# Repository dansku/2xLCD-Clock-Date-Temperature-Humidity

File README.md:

2xLCD Clock-Date-Temperature-Humidity

Under dev...

More at: danielandrade.net

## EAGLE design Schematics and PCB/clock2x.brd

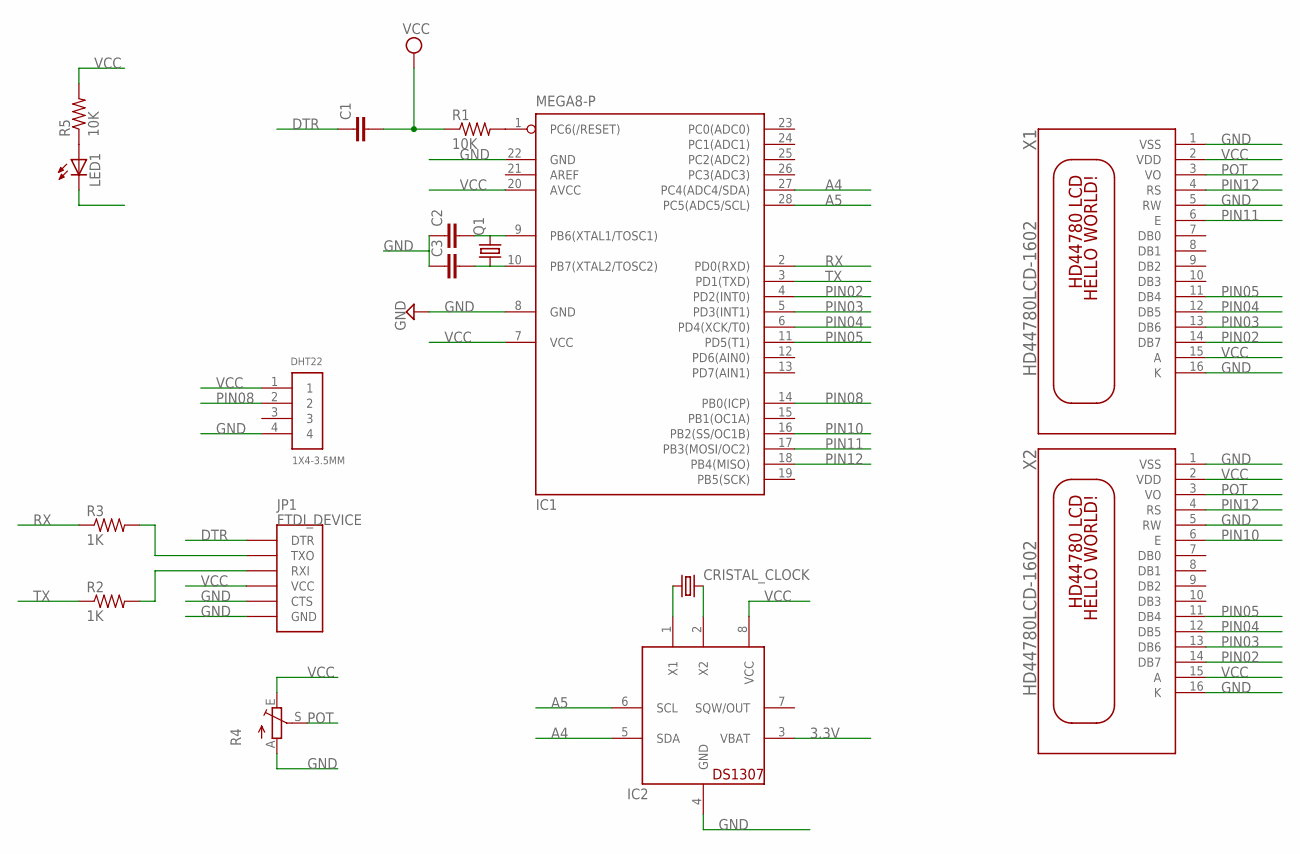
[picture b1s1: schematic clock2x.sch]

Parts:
C1, C2, C3: C5/2.5; C5B2.5
CRISTAL_CLOCK: CRYSTALTC26V; TC26V
DHT22: 1X4-3.5MM; 1X04-3.5MM
IC1: MEGA8-P; DIL28-3
IC2: DS1307; DIL08
JP1: FTDI_DEVICE; FTDI_DEVICE_SIDE
LED1: LED5MM
Q1: CRYSTALHC49S; HC49/S
R1, R5: 10K; 0207/12
R2, R3: 1K; 0207/12
R4: TRIM_EU-RJ9W; RJ9W
X1, X2: HD44780LCD-1602; LCD1602

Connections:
3.3V: IC2.3 (VBAT)
A4: IC1.27 (PC4(ADC4/SDA)), IC2.5 (SDA)
A5: IC1.28 (PC5(ADC5/SCL)), IC2.6 (SCL)
DTR: C1.1, JP1.P$1 (DTR)
GND: C2.1, C3.1, DHT22.4, IC1.8 (GND), IC1.22 (GND), IC2.4 (GND), JP1.P$5 (CTS), JP1.P$6 (GND), LED1.K (C), R4.A, X1.1 (VSS), X1.5 (RW), X1.16 (K), X2.1 (VSS), X2.5 (RW), X2.16 (K)
unnamed: IC1.1 (PC6(/RESET)), R1.2
unnamed: C2.2, IC1.9 (PB6(XTAL1/TOSC1)), Q1.2
unnamed: C3.2, IC1.10 (PB7(XTAL2/TOSC2)), Q1.1
unnamed: JP1.P$2 (TXO), R3.2
unnamed: JP1.P$3 (RXI), R2.2
unnamed: LED1.A, R5.1
unnamed: CRISTAL_CLOCK.1, IC2.1 (X1)
unnamed: CRISTAL_CLOCK.2, IC2.2 (X2)
PIN02: IC1.4 (PD2(INT0)), X1.14 (DB7), X2.14 (DB7)
PIN03: IC1.5 (PD3(INT1)), X1.13 (DB6), X2.13 (DB6)
PIN04: IC1.6 (PD4(XCK/T0)), X1.12 (DB5), X2.12 (DB5)
PIN05: IC1.11 (PD5(T1)), X1.11 (DB4), X2.11 (DB4)
PIN08: DHT22.2, IC1.14 (PB0(ICP))
PIN10: IC1.16 (PB2(SS/OC1B)), X2.6 (E)
PIN11: IC1.17 (PB3(MOSI/OC2)), X1.6 (E)
PIN12: IC1.18 (PB4(MISO)), X1.4 (RS), X2.4 (RS)
POT: R4.S, X1.3 (VO), X2.3 (VO)
RX: IC1.2 (PD0(RXD)), R3.1
TX: IC1.3 (PD1(TXD)), R2.1
VCC: C1.2, DHT22.1, IC1.7 (VCC), IC1.20 (AVCC), IC2.8 (VCC), JP1.P$4 (VCC), R1.1, R4.E, R5.2, X1.2 (VDD), X1.15 (A), X2.2 (VDD), X2.15 (A)

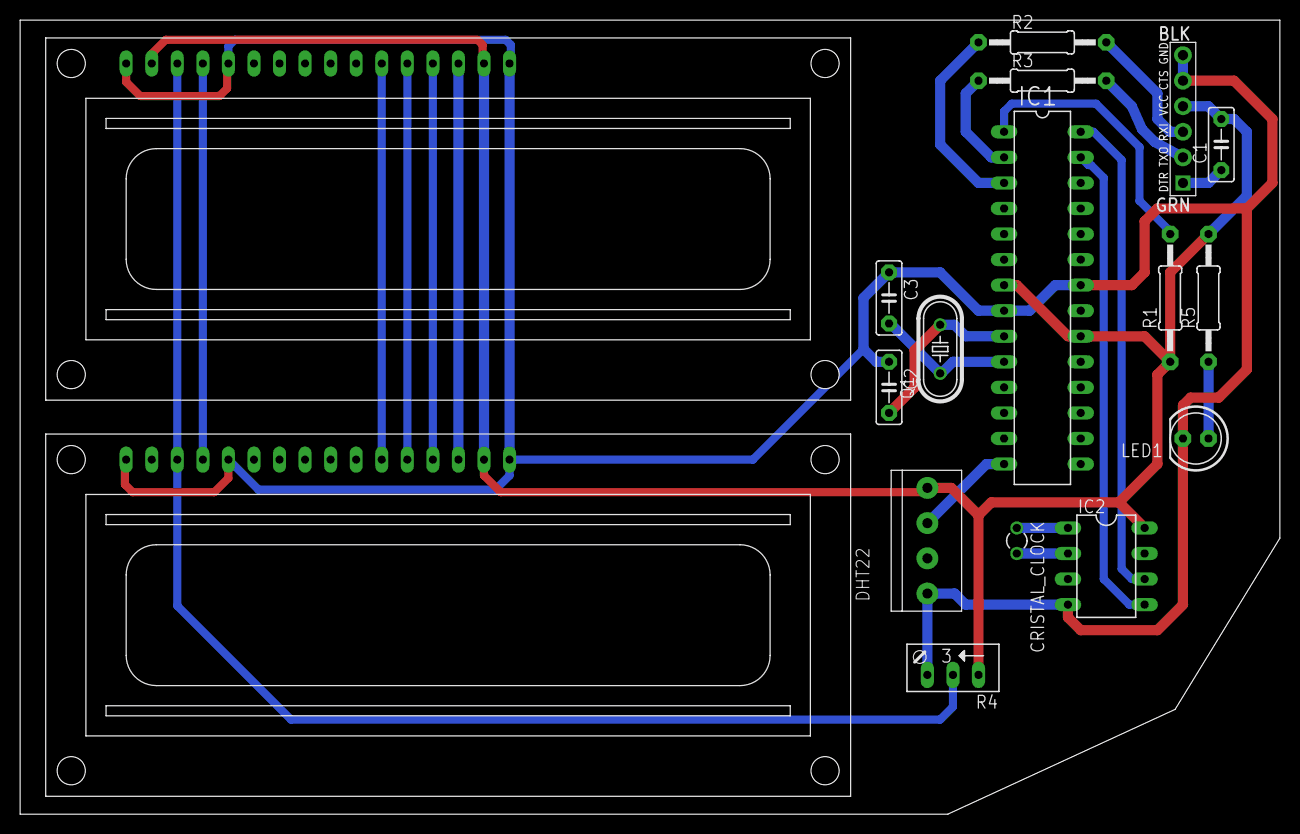
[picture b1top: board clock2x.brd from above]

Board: 2 copper layers, 125.2 x 78.9 mm, 17 parts (0 on the bottom side), 24 nets.

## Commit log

2013-09-21 First Commit
    Partlist
2013-09-21 fixing part list
2013-09-22 Starting to build PCB
2013-09-22 Creating folders
2013-09-22 fix readme

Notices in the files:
parts and their libraries:
SparkFun-Connectors: Licensing: CC v3.0 Share-Alike You are welcome to use this library for commercial purposes.
